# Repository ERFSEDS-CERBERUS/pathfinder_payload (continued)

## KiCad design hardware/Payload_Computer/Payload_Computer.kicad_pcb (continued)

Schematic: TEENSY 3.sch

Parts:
C901, C902: 0.1 uF; C_0603_1608Metric_Pad1.08x0.95mm_HandSolder
C903: C; C_0603_1608Metric_Pad1.08x0.95mm_HandSolder
D901: LED; LED_0603_1608Metric_Pad1.05x0.95mm_HandSolder
FB901, FB902: Ferrite_Bead_Small; C_0603_1608Metric_Pad1.08x0.95mm_HandSolder
R901: 470 OHM; R_0603_1608Metric_Pad0.98x0.95mm_HandSolder
R902: R_US; R_0603_1608Metric_Pad0.98x0.95mm_HandSolder
U901: MK20DX256VLH7; LQFP-64_10x10mm_P0.5mm

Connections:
+3V3: FB901.1, U901.3 (VCC), U901.7 (VOUT3V3), U901.21 (VBAT), U901.30 (VCC), U901.48 (VCC); also elsewhere on the board
/CS_BARO: U901.44 (D22/A8/PWM/TOUCH); also elsewhere on the board
/CS_BARO2: U901.64 (D5/PWM); also elsewhere on the board
/CS_FLASH: U901.41 (D32/PWM/TOUCH); also elsewhere on the board
/CS_SD: U901.38 (D18/A4/SDA0/TOUCH); also elsewhere on the board
/D2_+: U901.5 (USB-P); also elsewhere on the board
/D2_-: U901.6 (USB-M); also elsewhere on the board
/FANS: U901.42 (D25/PWM/TOUCH); also elsewhere on the board
/LED_BLUE: U901.35 (D16/A2/TOUCH); also elsewhere on the board
/LED_GREEN: U901.37 (D19/A5/SCL0/TOUCH); also elsewhere on the board
/LED_RED: U901.36 (D17/A3/TOUCH); also elsewhere on the board
/MISO: U901.52 (D12/MISO); also elsewhere on the board
/MOSI: U901.51 (D11/MOSI); also elsewhere on the board
/PTA0_2: U901.22 (PTA0); also elsewhere on the board
/PTA2_2: U901.24 (PTA2); also elsewhere on the board
/PTA3_2: U901.25 (PTA3); also elsewhere on the board
/RESET_TEENSY_2: U901.34 (RESET); also elsewhere on the board
/SCK: D901.2 (A), U901.50 (D13/SCK/LED); also elsewhere on the board
/SCL: U901.55 (D29/A18/SCL1); also elsewhere on the board
/SDA: U901.56 (D30/A19/SDA1); also elsewhere on the board
/SERVO5: U901.62 (D20/A6/PWM); also elsewhere on the board
/SERVO6: U901.63 (D21/A7/PWM); also elsewhere on the board
/XTAL1_2: U901.32 (OSC1); also elsewhere on the board
/XTAL2_2: U901.33 (OSC2); also elsewhere on the board
GND: FB902.1, R902.1, U901.4 (VSS), U901.31 (VSS), U901.47 (VSS); also elsewhere on the board
unnamed: C901.1, C902.1, C903.2, FB902.2, U901.15 (VREF-L), U901.16 (VSSA)
unnamed: C901.2, U901.17 (VREF_OUT)
unnamed: C902.2, R901.2, U901.14 (VREF-H)
unnamed: C903.1, FB901.2, R901.1, U901.13 (VCCA)
unnamed: D901.1 (K), R902.2

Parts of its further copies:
C1701, C1702: 0.1 uF; C_0603_1608Metric_Pad1.08x0.95mm_HandSolder
C1703: C; C_0603_1608Metric_Pad1.08x0.95mm_HandSolder
D1701: LED; LED_0603_1608Metric_Pad1.05x0.95mm_HandSolder
FB1701, FB1702: Ferrite_Bead_Small; C_0603_1608Metric_Pad1.08x0.95mm_HandSolder
R1701: 470 OHM; R_0603_1608Metric_Pad0.98x0.95mm_HandSolder
R1702: R_US; R_0603_1608Metric_Pad0.98x0.95mm_HandSolder
U1701: MK20DX256VLH7; LQFP-64_10x10mm_P0.5mm

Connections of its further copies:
+3V3: FB1701.1, U1701.3 (VCC), U1701.7 (VOUT3V3), U1701.21 (VBAT), U1701.30 (VCC), U1701.48 (VCC); also elsewhere on the board
/D1_+: U1701.5 (USB-P); also elsewhere on the board
/D1_-: U1701.6 (USB-M); also elsewhere on the board
/PTA0_1: U1701.22 (PTA0); also elsewhere on the board
/PTA2_1: U1701.24 (PTA2); also elsewhere on the board
/PTA3_1: U1701.25 (PTA3); also elsewhere on the board
/RESET_TEENSY_1: U1701.34 (RESET); also elsewhere on the board
/SERVO1: U1701.62 (D20/A6/PWM); also elsewhere on the board
/SERVO2: U1701.63 (D21/A7/PWM); also elsewhere on the board
/SERVO3: U1701.44 (D22/A8/PWM/TOUCH); also elsewhere on the board
/SERVO4: U1701.64 (D5/PWM); also elsewhere on the board
/TEENSY3.2_1/D25: U1701.42 (D25/PWM/TOUCH)
/TEENSY3.2_1/FLASH_CS: U1701.41 (D32/PWM/TOUCH)
/TEENSY3.2_1/LED_BLUE: U1701.36 (D17/A3/TOUCH)
/TEENSY3.2_1/LED_GREEN: U1701.37 (D19/A5/SCL0/TOUCH)
/TEENSY3.2_1/LED_RED: U1701.35 (D16/A2/TOUCH)
/TEENSY3.2_1/MISO: U1701.52 (D12/MISO)
/TEENSY3.2_1/MOSI: U1701.51 (D11/MOSI)
/TEENSY3.2_1/SCK: D1701.2 (A), U1701.50 (D13/SCK/LED)
/TEENSY3.2_1/SCL: U1701.55 (D29/A18/SCL1)
/TEENSY3.2_1/SDA: U1701.56 (D30/A19/SDA1)
/TEENSY3.2_1/SD_FLASH: U1701.38 (D18/A4/SDA0/TOUCH)
/XTAL1_1: U1701.32 (OSC1); also elsewhere on the board
/XTAL2_1: U1701.33 (OSC2); also elsewhere on the board
GND: FB1702.1, R1702.1, U1701.4 (VSS), U1701.31 (VSS), U1701.47 (VSS); also elsewhere on the board
unnamed: C1701.1, C1702.1, C1703.2, FB1702.2, U1701.15 (VREF-L), U1701.16 (VSSA)
unnamed: C1701.2, U1701.17 (VREF_OUT)
unnamed: C1702.2, R1701.2, U1701.14 (VREF-H)
unnamed: C1703.1, FB1701.2, R1701.1, U1701.13 (VCCA)
unnamed: D1701.1 (K), R1702.2

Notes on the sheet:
TEENSY DATA TRANSFER LIGHT

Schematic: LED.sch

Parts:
D1901: LED_ABGR; LED
R1901, R1902, R1903: R_US; R_0603_1608Metric_Pad0.98x0.95mm_HandSolder

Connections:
+3V3: D1901.1 (A); also elsewhere on the board
/LED_BLUE: R1903.2; also elsewhere on the board
/LED_GREEN: R1902.2; also elsewhere on the board
/LED_RED: R1901.2; also elsewhere on the board
unnamed: D1901.2 (BK), R1903.1
unnamed: D1901.3 (GK), R1902.1
unnamed: D1901.4 (RK), R1901.1

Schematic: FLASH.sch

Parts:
C2001: 100nF; C_0603_1608Metric_Pad1.08x0.95mm_HandSolder
U2001: W25N01GVZEIG_TR; SON127P800X600X80-9N

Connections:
+3V3: C2001.2, U2001.8 (VCC); also elsewhere on the board
/CS_FLASH: U2001.1 (/CS); also elsewhere on the board
/MISO: U2001.2 (DO(IO1)); also elsewhere on the board
/MOSI: U2001.5 (DI(IO0)); also elsewhere on the board
/SCK: U2001.6 (CLK); also elsewhere on the board
GND: C2001.1, U2001.3 (/WP(IO2)), U2001.4 (GND), U2001.7 (/HOLD(IO3)); also elsewhere on the board

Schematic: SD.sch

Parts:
C2101: 100nF; C_0603_1608Metric_Pad1.08x0.95mm_HandSolder
J2102: 503398-1892; MOLEX_503398-1892; PARTREV 0

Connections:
+3V3: C2101.2, J2102.4 (VDD); also elsewhere on the board
/CS_SD: J2102.2 (CD/DAT3^2); also elsewhere on the board
/MISO: J2102.7 (DAT0); also elsewhere on the board
/MOSI: J2102.3 (CMD); also elsewhere on the board
/SCK: J2102.5 (CLK); also elsewhere on the board
GND: C2101.1, J2102.6 (VSS), J2102.9 (VSS), J2102.P1 (SHIELD), J2102.P2 (SHIELD), J2102.P3 (SHIELD), J2102.P4 (SHIELD); also elsewhere on the board

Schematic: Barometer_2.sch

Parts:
J2101: 0532610671; MOLEX_0532610671

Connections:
+3V3: J2101.2; also elsewhere on the board
/CS_BARO2: J2101.6; also elsewhere on the board
/MISO: J2101.4; also elsewhere on the board
/MOSI: J2101.3; also elsewhere on the board
/SCK: J2101.5; also elsewhere on the board
GND: J2101.1, J2101.S1 (SHIELD), J2101.S2 (SHIELD); also elsewhere on the board

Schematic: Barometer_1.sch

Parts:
C2201, C2202: 100nF; C_0603_1608Metric_Pad1.08x0.95mm_HandSolder
U2201: BME280; Bosch_LGA-8_2.5x2.5mm_P0.65mm_ClockwisePinNumbering

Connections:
+3V3: C2201.2, C2202.2, U2201.6 (VDDIO), U2201.8 (VDD); also elsewhere on the board
/CS_BARO: U2201.2 (CSB); also elsewhere on the board
/MISO: U2201.5 (SDO); also elsewhere on the board
/MOSI: U2201.3 (SDI); also elsewhere on the board
/SCK: U2201.4 (SCK); also elsewhere on the board
GND: C2201.1, C2202.1, U2201.1 (GND), U2201.7 (GND); also elsewhere on the board

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
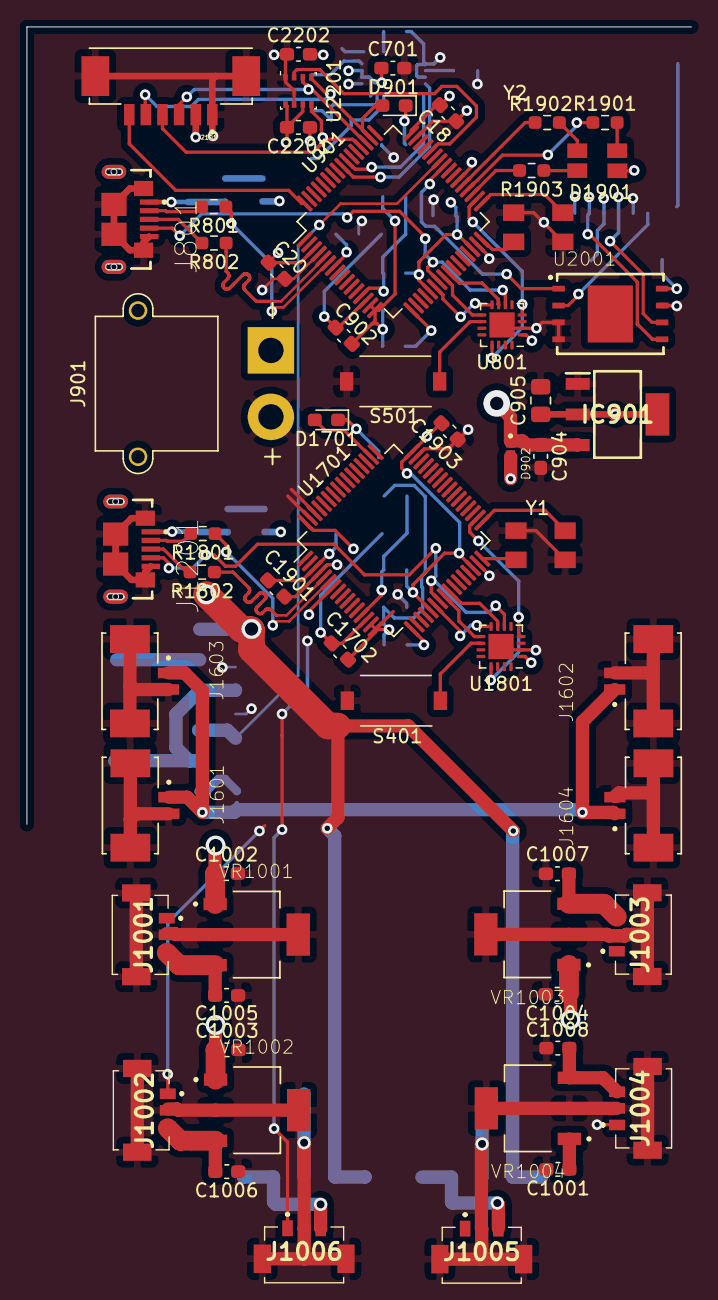
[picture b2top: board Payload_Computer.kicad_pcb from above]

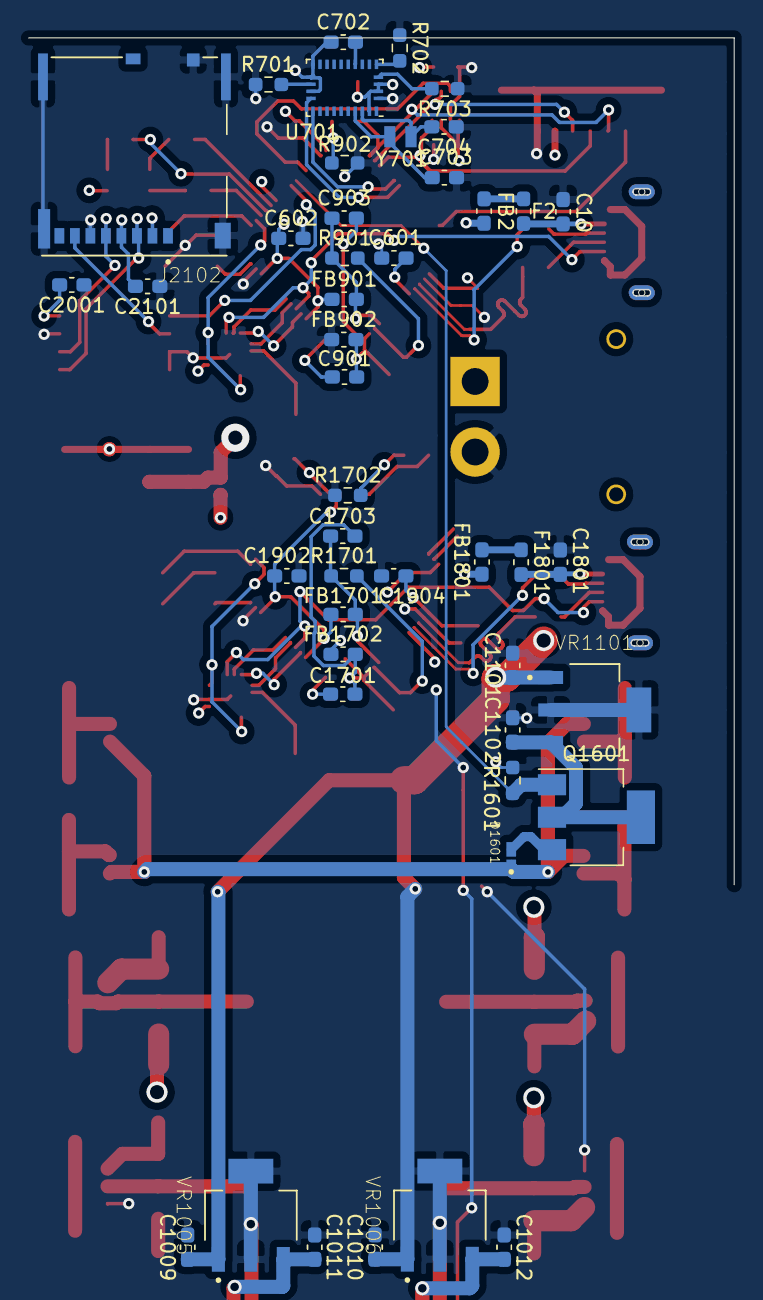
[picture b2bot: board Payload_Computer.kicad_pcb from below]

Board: 4 copper layers, 108 parts (45 on the bottom side), 78 nets.

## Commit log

2020-09-09 Added .gitignore
2020-09-25 Added initial documentation and tasks
2020-09-25 Minor updates
2020-09-26 Added Spreadsheet for power analysis
2020-09-27 Added microcontroller and FTDI chip for analysis
2020-10-12 Added original Kicad files
2020-10-12 Added Processors
2020-10-12 Added FTDI and crystals
2020-10-12 Added FTDI
2020-10-19 Minor updates to FTDI
2020-10-19 Added reset circuits
2020-10-19 Added ICSP headers
2020-10-27 Finished ICSP. Added a few leds and filtering caps
2020-10-27 Moved gitignore
2020-10-27 Modified Gitignore
2020-10-27 Deleted excess files
2020-10-29 Adding BNO055 Sensor
    Currently in the process of adding the sensor to the schematic.
2020-10-30 Still adding rest of the schematic
    I have added the BNO055, but I need to finish the pin headers and power converter from 3v - 5v
2020-11-02 Finished BNO055
2020-11-05 Made the CAPS on the clock in parallel, not series
2020-11-05 Updated Gitignore
2020-11-05 Cleaned up Files
2020-11-05 I'm dumb... changed CAPS on clock to parallel
2020-11-05 Changed formatting
2020-11-13 Added a new processor. Fixed up some libraries. Did some schematic work.
2020-11-15 Minor Changes
2020-11-28 Added a power regulation sheet. Added indication LED for Teensy. Fixed Teensy filtering
2020-11-29 Updated IMU Datasheet
2020-12-01 Added Servo Motor Sheets and regulators. Added Fan Sheets
2020-12-15 Minor Library Changes
2020-12-15 Fucking Gitignore
2020-12-15 More Library Updates
2020-12-16 Added Barometer, need to find Teensy SPI pin
2020-12-23 Changed CAP values
2021-02-13 Updated processor for arduino. Fixed schematic a bit
2021-02-13 Finished Fan Schematic. Working on Servos
2021-02-17 Added some footprints
2021-02-18 Added footprints to fuse and led
2021-02-20 Added LED to board
2021-02-20 Added SD card and Battery Connector
2021-02-20 Added footprints to led
2021-02-21 Added last footprints and started routing
2021-02-21 Continued all routing
2021-02-23 Annotated a few things
2021-02-23 Did some routing
2021-02-23 quick update
2021-02-24 More Routing Work
2021-02-24 Updated LED. Need to fix Mosfet footprint
2021-02-25 More Routing
2021-02-25 Did some more routing. Need to really work on condensing some things
2021-03-06 More Changes
2021-03-20 Added Voltage Regulator
2021-03-23 Finished the overbuilt power supply and did some minor routing
2021-03-24 I did something
2021-03-27 More routing and added BNO055
2021-04-03 Added SD card reader
2021-04-03 Did some stuff
2021-04-10 Finished some routing
